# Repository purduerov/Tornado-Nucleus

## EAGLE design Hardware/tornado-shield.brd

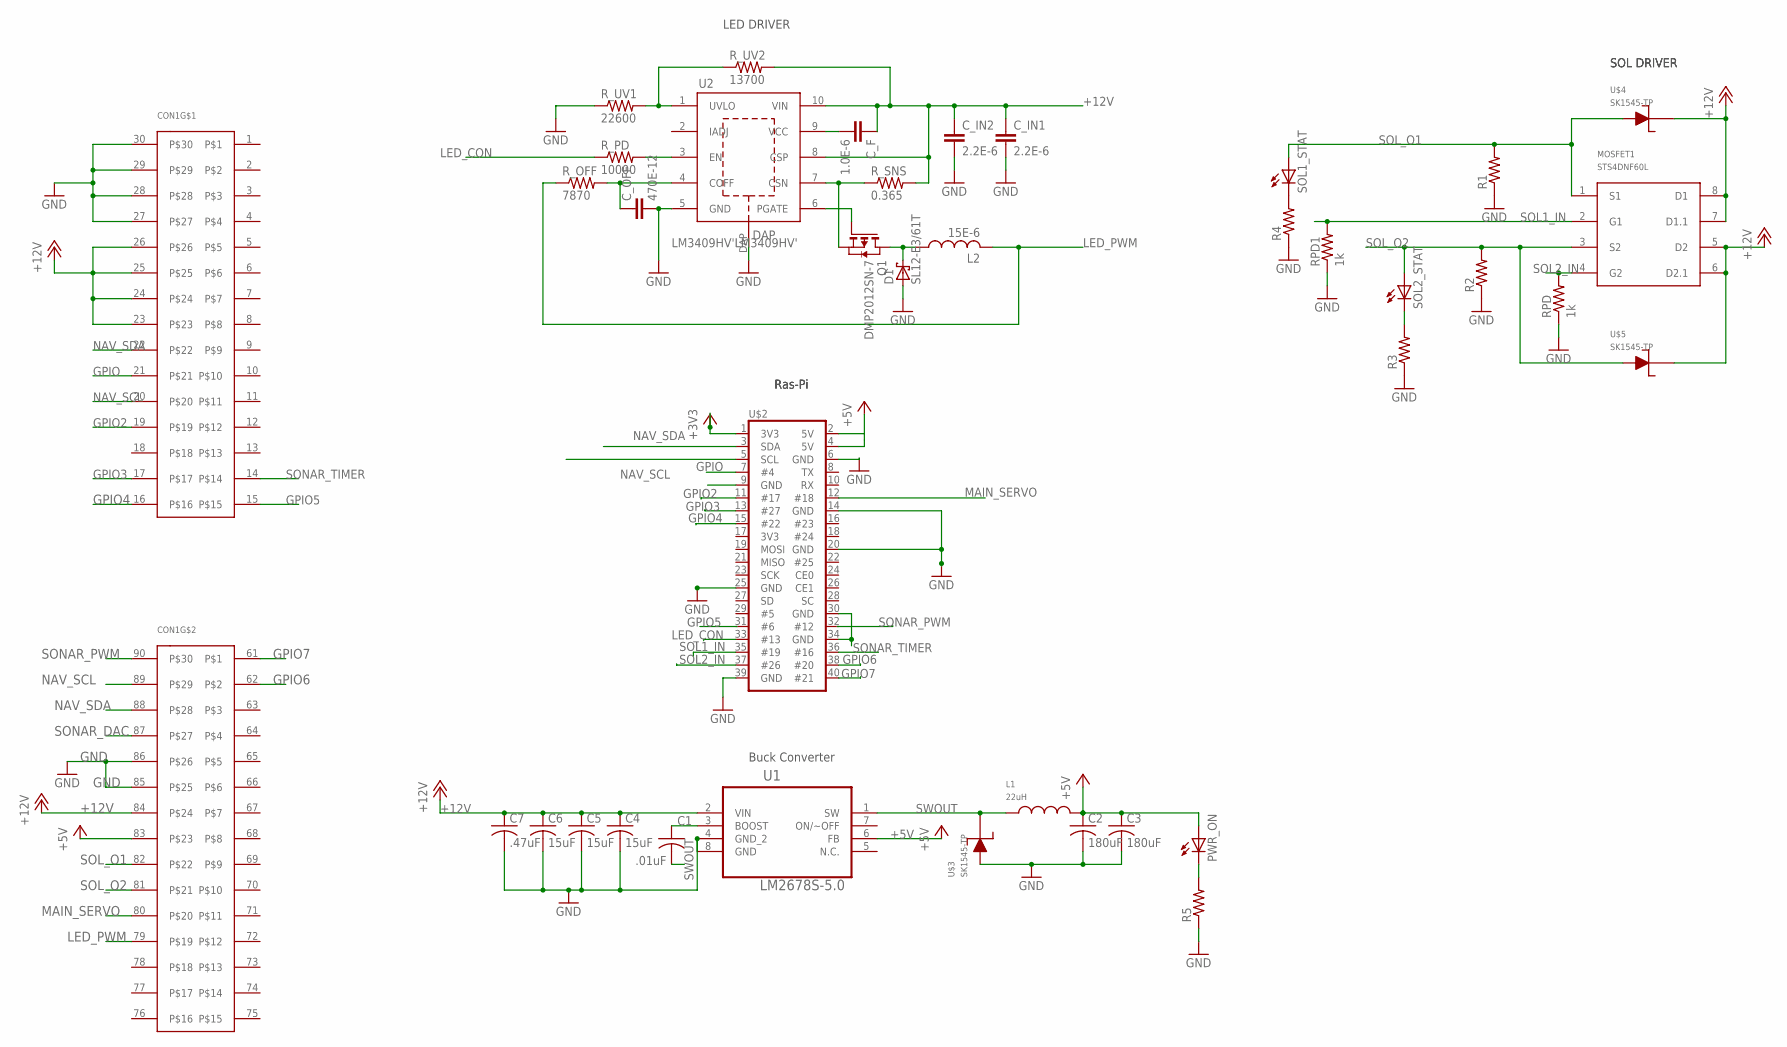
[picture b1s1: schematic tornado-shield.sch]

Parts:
C1: .01uF; C0603
C2, C3: 180uF; C0603
C4, C5, C6: 15uF; C0603
C7: .47uF; C0603
CON1: ROV_SHIELD_V2
C_F: 1.0E-6; C0603
C_IN1, C_IN2: 2.2E-6; C0603
C_OFF: 470E-12; C0402
D1: SL12-E3/61T
L1: 22uH; 7443551221
L2: 15E-6; SRN8040
MOSFET1: STS4DNF60L; SO08
PWR_ON: LED_ESML0603; LED_SML0603
Q1: DMP2012SN-7
R1, R2, R3, R4, R5: R-US_R0603; R0603
RPD, RPD1: 1k; R0603
R_OFF: 7870; R0603
R_PD: 10000; R0603
R_SNS: 0.365; R2512
R_UV1: 22600; R0603
R_UV2: 13700; R0603
SOL1_STAT, SOL2_STAT: LED_ESML0603; LED_SML0603
U1: LM2678S-5.0; TO127P1435X457-8N
U2: LM3409HV'LM3409HV'; VSSOP-10
U$2: RASPBERRY-PI-2
U$3, U$4, U$5: SK1545-TP; DO-214AB

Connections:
+3V3: U$2.1 (3V3)
+5V: C2.1, C3.1, CON1.83, L1.P$2, PWR_ON.A, U1.6 (FB), U$2.2 (5V), U$2.4 (5V)
+12V: C4.1, C5.1, C6.1, C7.1, CON1.23, CON1.24, CON1.25, CON1.26, CON1.84, C_F.1, C_IN1.1, C_IN2.1, MOSFET1.5 (D2), MOSFET1.6 (D2.1), MOSFET1.7 (D1.1), MOSFET1.8 (D1), R_SNS.2, R_UV2.2, U1.2 (VIN), U2.8 (CSP), U2.10 (VIN), U$4.P$2, U$5.P$2
GND: C2.2, C3.2, C4.2, C5.2, C6.2, C7.2, CON1.27, CON1.28, CON1.29, CON1.30, CON1.85, CON1.86, C_IN1.2, C_IN2.2, C_OFF.2, D1.2 (A), R1.1, R2.1, R3.1, R4.1, R5.1, RPD.1, RPD1.1, R_UV1.1, U1.4 (GND_2), U1.8 (GND), U2.5 (GND), U2.DAP, U$2.6 (GND), U$2.9 (GND), U$2.14 (GND), U$2.20 (GND), U$2.25 (GND), U$2.30 (GND), U$2.34 (GND), U$2.39 (GND), U$3.P$1
GPIO: CON1.21, U$2.7 (#4)
GPIO2: CON1.19, U$2.11 (#17)
GPIO3: CON1.17, U$2.13 (#27)
GPIO4: CON1.16, U$2.15 (#22)
GPIO5: CON1.15, U$2.31 (#6)
GPIO6: CON1.62, U$2.38 (#20)
GPIO7: CON1.61, U$2.40 (#21)
L1: D1.1 (C), L2.1, Q1.1 (D)
LED_CON: R_PD.1, U$2.33 (#13)
LED_PWM: CON1.79, L2.2, R_OFF.1
MAIN_SERVO: CON1.80, U$2.12 (#18)
unnamed: C_OFF.1, R_OFF.2, U2.4 (COFF)
unnamed: R_UV1.2, R_UV2.1, U2.1 (UVLO)
unnamed: C1.1, U1.3 (BOOST)
unnamed: C_F.2, U2.9 (VCC)
unnamed: R_PD.2, U2.3 (EN)
unnamed: Q1.2 (G), U2.6 (PGATE)
unnamed: Q1.3 (S), R_SNS.1, U2.7 (CSN)
unnamed: R4.2, SOL1_STAT.C
unnamed: PWR_ON.C, R5.2
NAV_SCL: CON1.20, CON1.89, U$2.5 (SCL)
NAV_SDA: CON1.22, CON1.88, U$2.3 (SDA)
SOL1_IN: MOSFET1.2 (G1), RPD1.2, U$2.35 (#19)
SOL2_IN: MOSFET1.4 (G2), RPD.2, U$2.37 (#26)
SOL2_STAT: R3.2, SOL2_STAT.C
SOL_O1: CON1.82, MOSFET1.1 (S1), R1.2, SOL1_STAT.A, U$4.P$1
SOL_O2: CON1.81, MOSFET1.3 (S2), R2.2, SOL2_STAT.A, U$5.P$1
SONAR_DAC: CON1.87
SONAR_PWM: CON1.90, U$2.32 (#12)
SONAR_TIMER: CON1.14, U$2.36 (#16)
SWOUT: C1.2, L1.P$1, U1.1 (SW), U$3.P$2

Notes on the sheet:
LED DRIVER
Ras-Pi
Buck Converter
SOL DRIVER

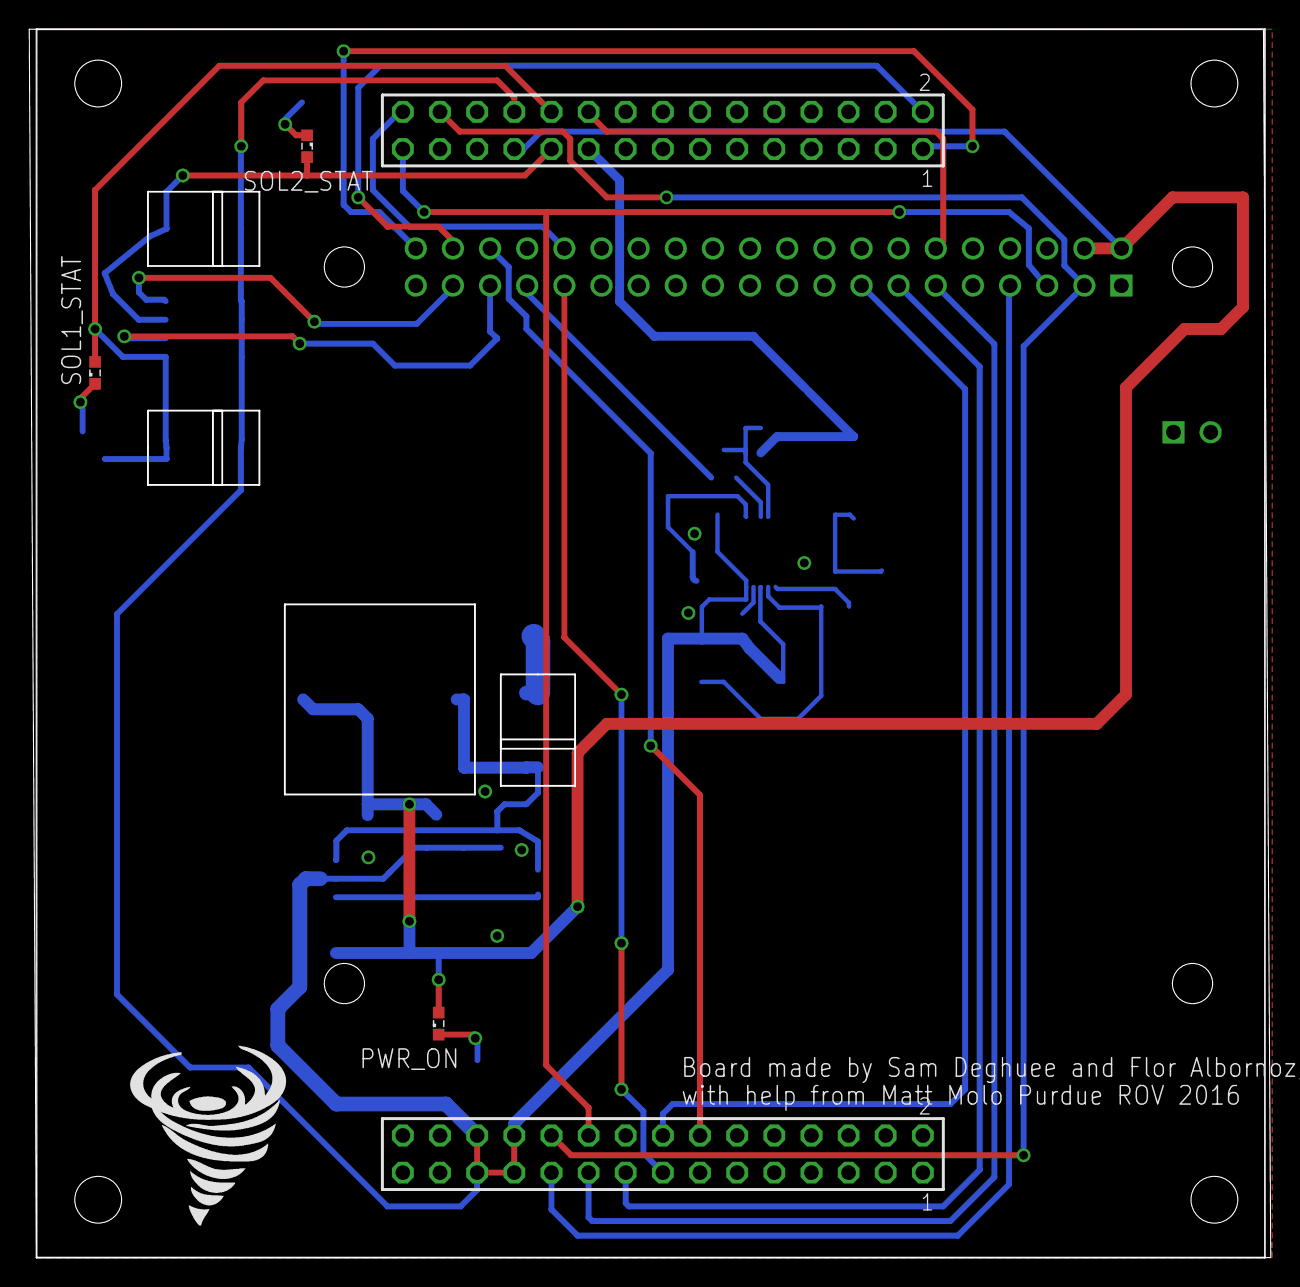
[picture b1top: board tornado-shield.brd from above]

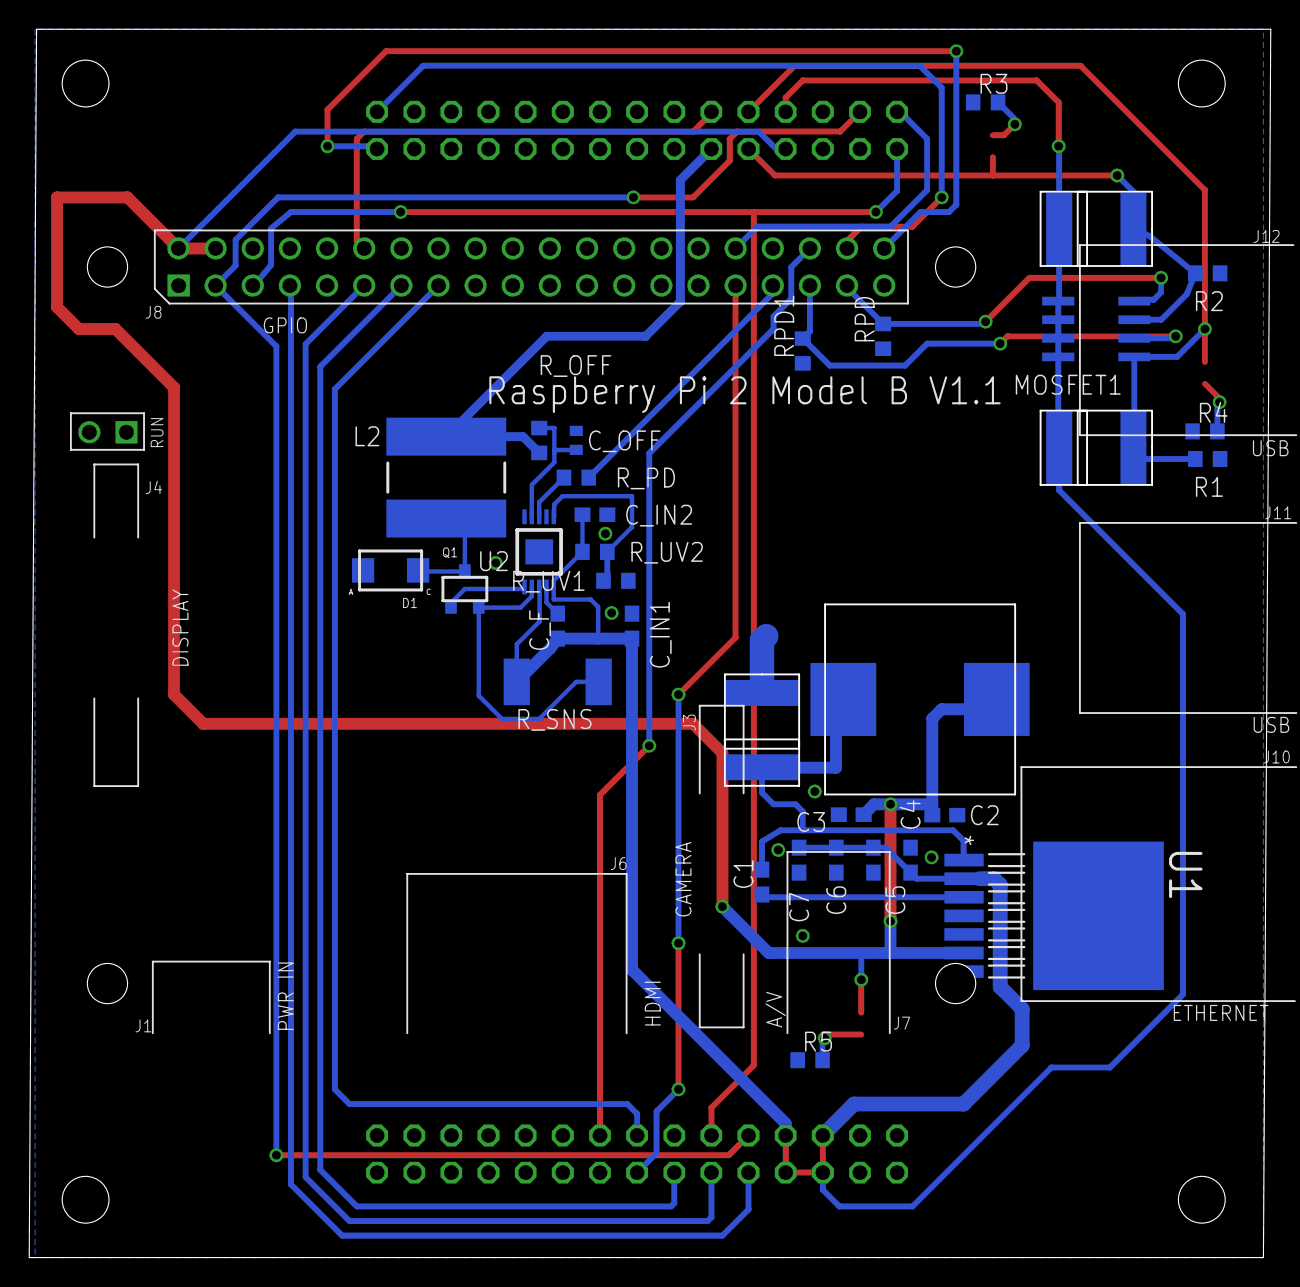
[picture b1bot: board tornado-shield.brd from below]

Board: 2 copper layers, 84.8 x 83.9 mm, 38 parts (34 on the bottom side), 33 nets.

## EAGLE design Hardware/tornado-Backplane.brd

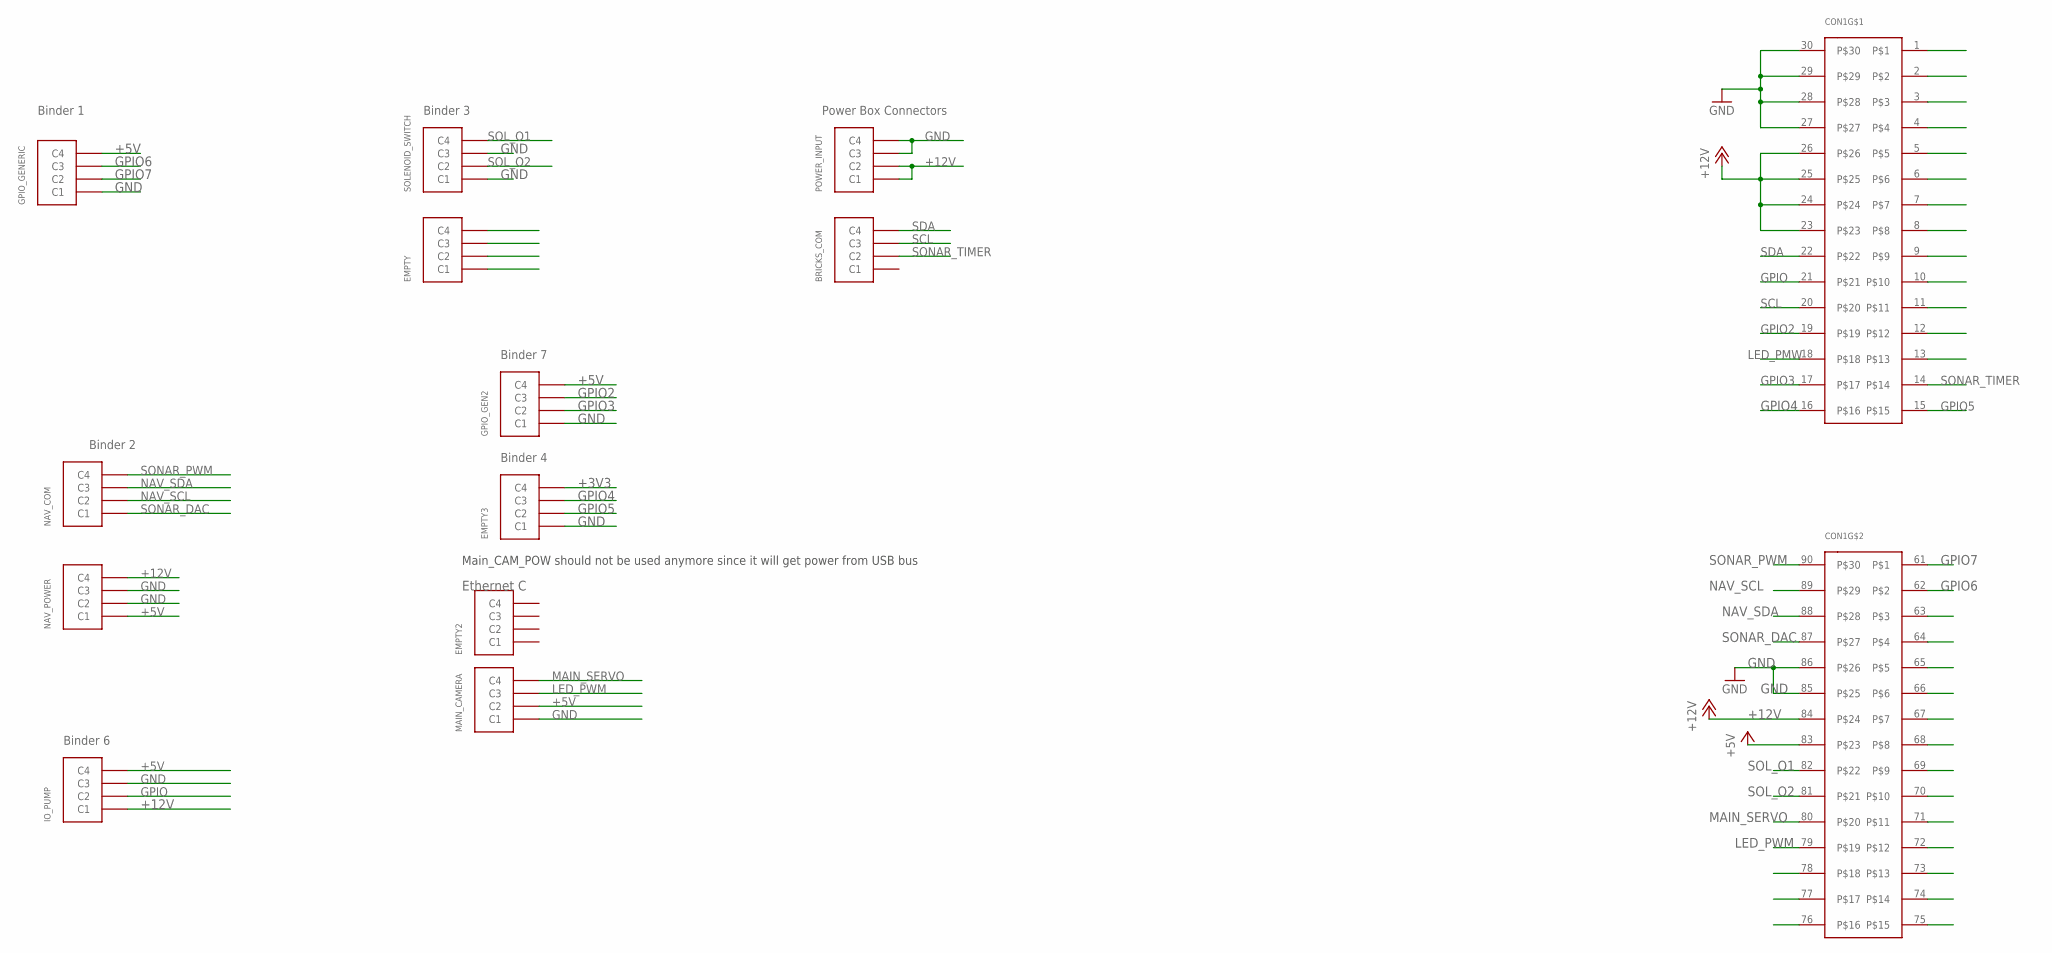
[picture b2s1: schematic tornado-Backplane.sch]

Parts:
BRICKS_COM: MICRO-FIT-4-SMD-PART; MICRO-FIT-4-SMD
CON1: ROV_SHIELD_V2
EMPTY, EMPTY2, EMPTY3: MICRO-FIT-4-SMD-PART; MICRO-FIT-4-SMD
GPIO_GEN2: MICRO-FIT-4-SMD-PART; MICRO-FIT-4-SMD
GPIO_GENERIC: MICRO-FIT-4-SMD-PART; MICRO-FIT-4-SMD
IO_PUMP: MICRO-FIT-4-SMD-PART; MICRO-FIT-4-SMD
MAIN_CAMERA: MICRO-FIT-4-SMD-PART; MICRO-FIT-4-SMD
NAV_COM: MICRO-FIT-4-SMD-PART; MICRO-FIT-4-SMD
NAV_POWER: MICRO-FIT-4-SMD-PART; MICRO-FIT-4-SMD
POWER_INPUT: MICRO-FIT-4-SMD-PART; MICRO-FIT-4-SMD
SOLENOID_SWITCH: MICRO-FIT-4-SMD-PART; MICRO-FIT-4-SMD

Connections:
+3V3: EMPTY3.C4
+5V: CON1.83, GPIO_GEN2.C4, GPIO_GENERIC.C4, IO_PUMP.C4, MAIN_CAMERA.C2, NAV_POWER.C1
+12V: CON1.23, CON1.24, CON1.25, CON1.26, CON1.84, IO_PUMP.C1, NAV_POWER.C4, POWER_INPUT.C1, POWER_INPUT.C2
GND: CON1.27, CON1.28, CON1.29, CON1.30, CON1.85, CON1.86, EMPTY3.C1, GPIO_GEN2.C1, GPIO_GENERIC.C1, IO_PUMP.C3, MAIN_CAMERA.C1, NAV_POWER.C2, NAV_POWER.C3, POWER_INPUT.C3, POWER_INPUT.C4, SOLENOID_SWITCH.C1, SOLENOID_SWITCH.C3
GPIO: CON1.21, IO_PUMP.C2
GPIO2: CON1.19, GPIO_GEN2.C3
GPIO3: CON1.17, GPIO_GEN2.C2
GPIO4: CON1.16, EMPTY3.C3
GPIO5: CON1.15, EMPTY3.C2
GPIO6: CON1.62, GPIO_GENERIC.C3
GPIO7: CON1.61, GPIO_GENERIC.C2
KJ: CON1.77
LED_PMW: CON1.18
LED_PWM: CON1.79, MAIN_CAMERA.C3
MAIN_SERVO: CON1.80, MAIN_CAMERA.C4
NAV_SCL: CON1.89, NAV_COM.C2
NAV_SDA: CON1.88, NAV_COM.C3
SCL: BRICKS_COM.C3, CON1.20
SDA: BRICKS_COM.C4, CON1.22
SOL_O1: CON1.82, SOLENOID_SWITCH.C4
SOL_O2: CON1.81, SOLENOID_SWITCH.C2
SONAR_DAC: CON1.87, NAV_COM.C1
SONAR_PWM: CON1.90, NAV_COM.C4
SONAR_TIMER: BRICKS_COM.C2, CON1.14

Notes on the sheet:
Main_CAM_POW should not be used anymore since it will get power from USB bus
Power Box Connectors
Binder 2
Binder 1
Binder 3
Binder 7
Binder 4
Binder 6
Ethernet C

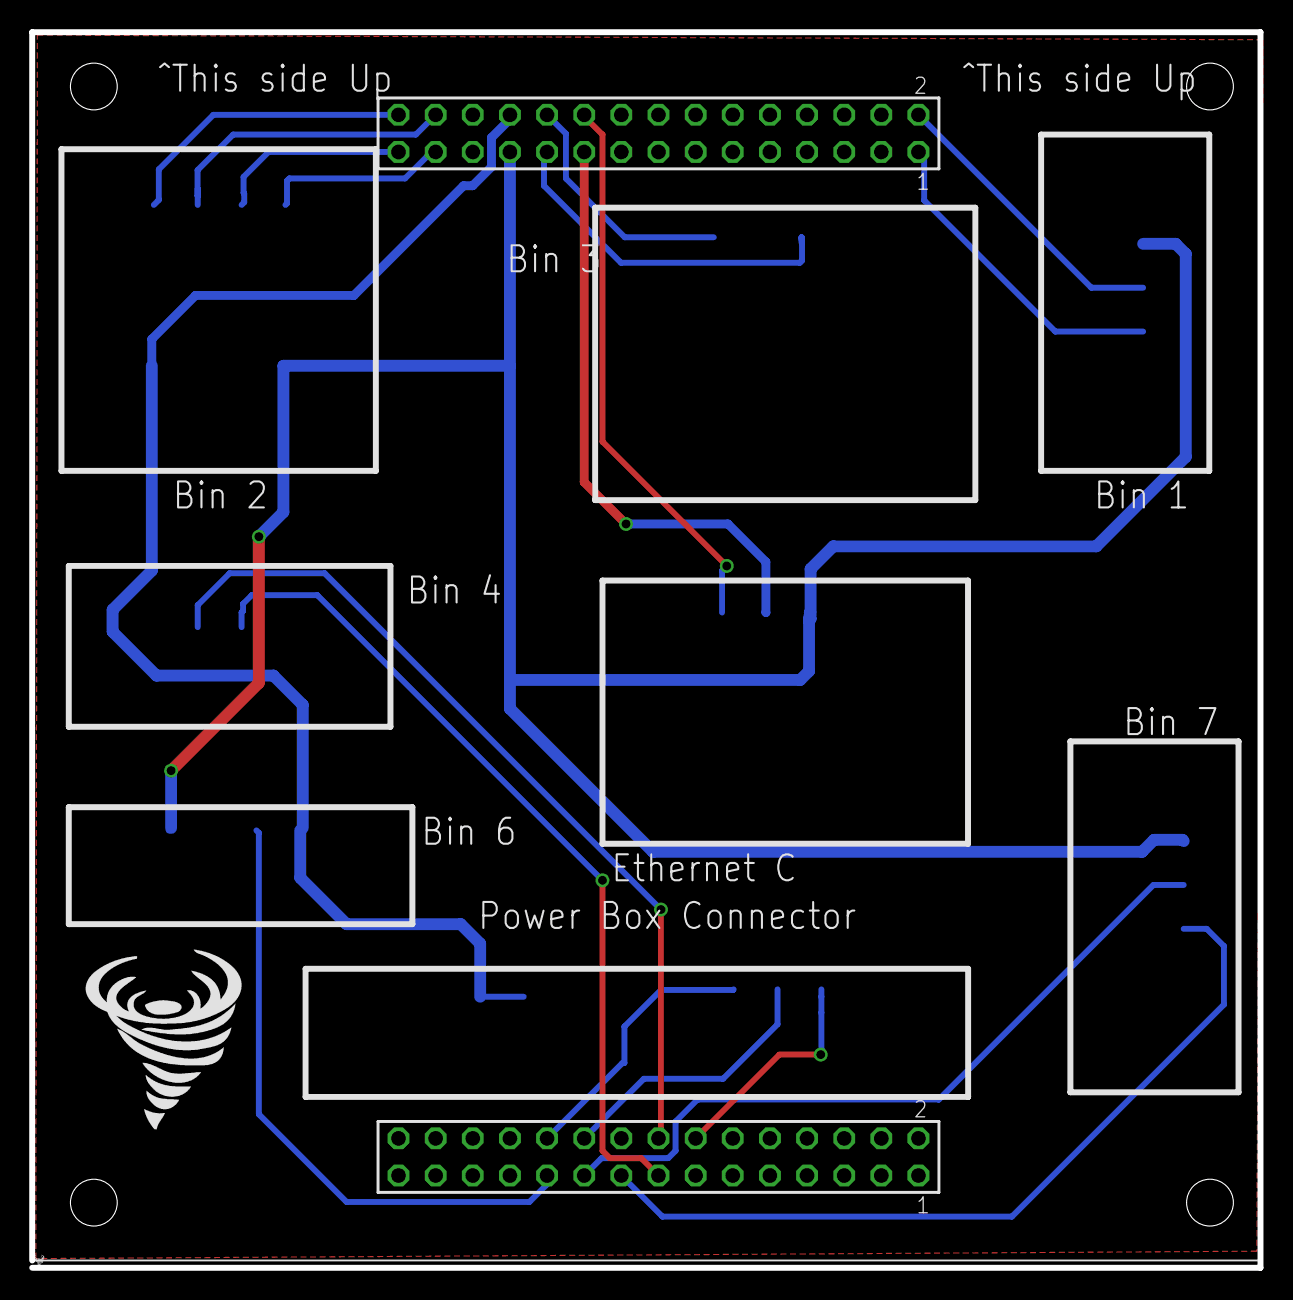
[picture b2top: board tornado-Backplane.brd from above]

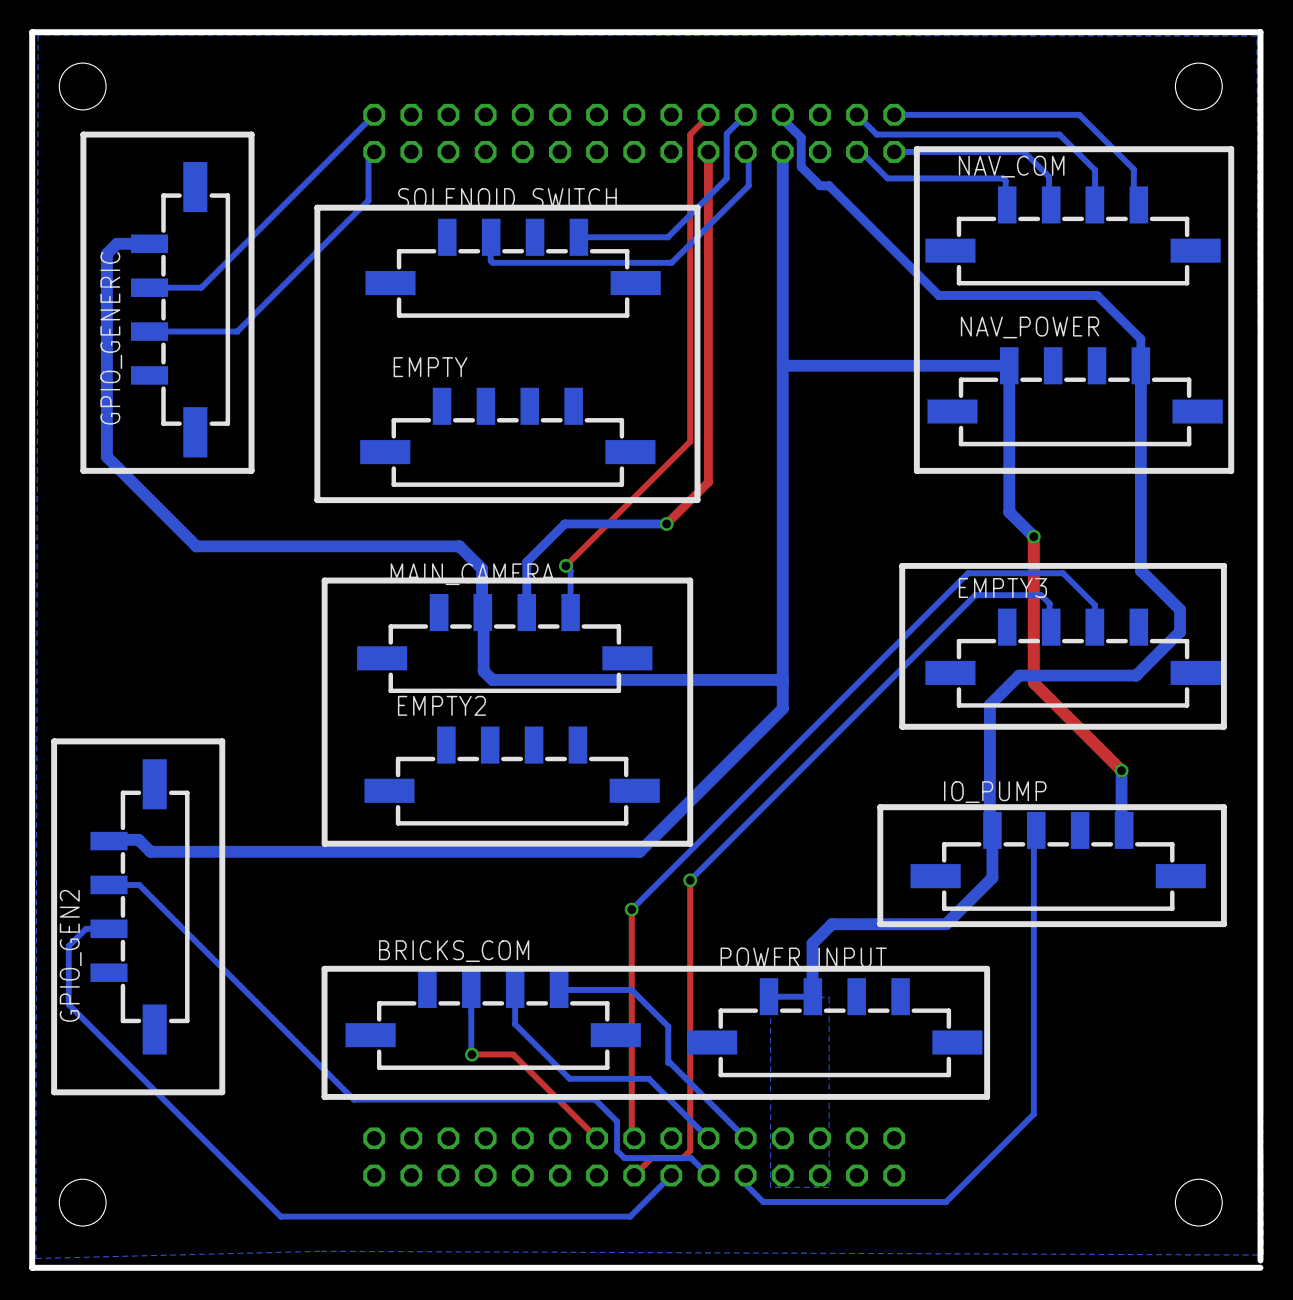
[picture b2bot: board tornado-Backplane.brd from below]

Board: 2 copper layers, 84.0 x 84.5 mm, 13 parts (12 on the bottom side), 21 nets.

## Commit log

2016-07-23 basic flask app
2016-07-24 Initial performace testing
2016-09-06 Added PCB boards
    Added hardware and added folders for software and hardware
2016-09-28 Updated the Tornado hardware to include the pinout of the stack and some additional routing
2016-09-30 Continued to finish Shield
    Still needs Pi Pinout
2016-09-30 added ignore file
2016-09-30 Removed backups
2016-09-30 Wrapping up initial board layout
2016-10-01 Board Design Rev 1.0
2016-10-02 Post Nick recomendations
2016-10-02 Fixes from Michael
    Mostly layout, fixing ground islands, and other small fixes.
2016-10-02 Fixed small problem with buck layout
2016-10-02 Added Status LEDs for power and Solenoids
2016-10-04 Added a new file for the read me. Needs to be updated to not be a joke
